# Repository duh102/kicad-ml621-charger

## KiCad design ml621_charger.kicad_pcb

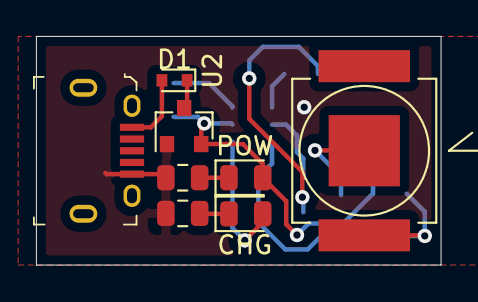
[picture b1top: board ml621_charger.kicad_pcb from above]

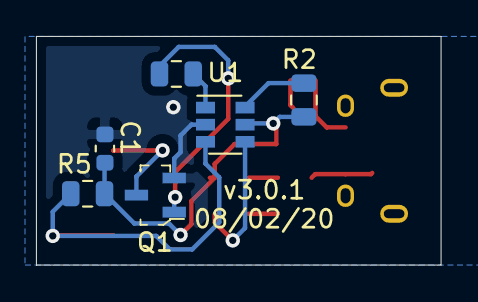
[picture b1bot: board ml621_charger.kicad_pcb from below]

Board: 2 copper layers, 22.5 x 12.7 mm, 14 parts (6 on the bottom side), 12 nets.

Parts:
BT1: ML621; BatteryHolder_Keystone_2998_621_6.8x2.2mm
C1: 0.1uF; C_0603_1608Metric
D1: 500mV; D_SOD-523
D2, D3: LED; LED_0805_2012Metric
J1: USB_B_Micro; USB_Micro_B_Female_10118194-0001LF
Q1: BSS138; SOT-23-3
R1, R3, R4: 20R; R_0805_2012Metric
R2: 10kR; R_0805_2012Metric
R5: 1kR; R_0805_2012Metric
U1: ATtiny10-TS; SOT-23-6
U2: AMS1117-3.3; SOT-23

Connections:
BGATE: R4.1, U1.1
GND: C1.2, J1.5, Q1.2, R1.2, R3.1, U1.2, U2.1
unnamed: BT1.2, Q1.3
unnamed: D1.1, U2.3
unnamed: D2.1, R1.1
unnamed: D3.1, R3.2
unnamed: D3.2, U1.4
unnamed: Q1.1, R4.2
unnamed: R2.1, U1.6
VBAT: BT1.1, R5.1, U1.3
VSUPPLY: D1.2, J1.1
V_REG: C1.1, D2.2, R2.2, R5.2, U1.5, U2.2

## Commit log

2019-09-24 Add schottkey diode to ensure reverse protection
2019-09-24 Fix battery holder polarity
2019-09-24 Fix schottkey diode rating
2019-12-16 Put USB connector directly on; add indicator LEDs
2019-12-16 Change around some values
2020-05-25 V3 with a microcontroller
2020-12-09 Fix charger
